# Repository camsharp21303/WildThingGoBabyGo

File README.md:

# WildThingGoBabyGo
All the files and designs for using a wild thing for Go Baby Go. Created from programming department on FTC team 10523 the dragons

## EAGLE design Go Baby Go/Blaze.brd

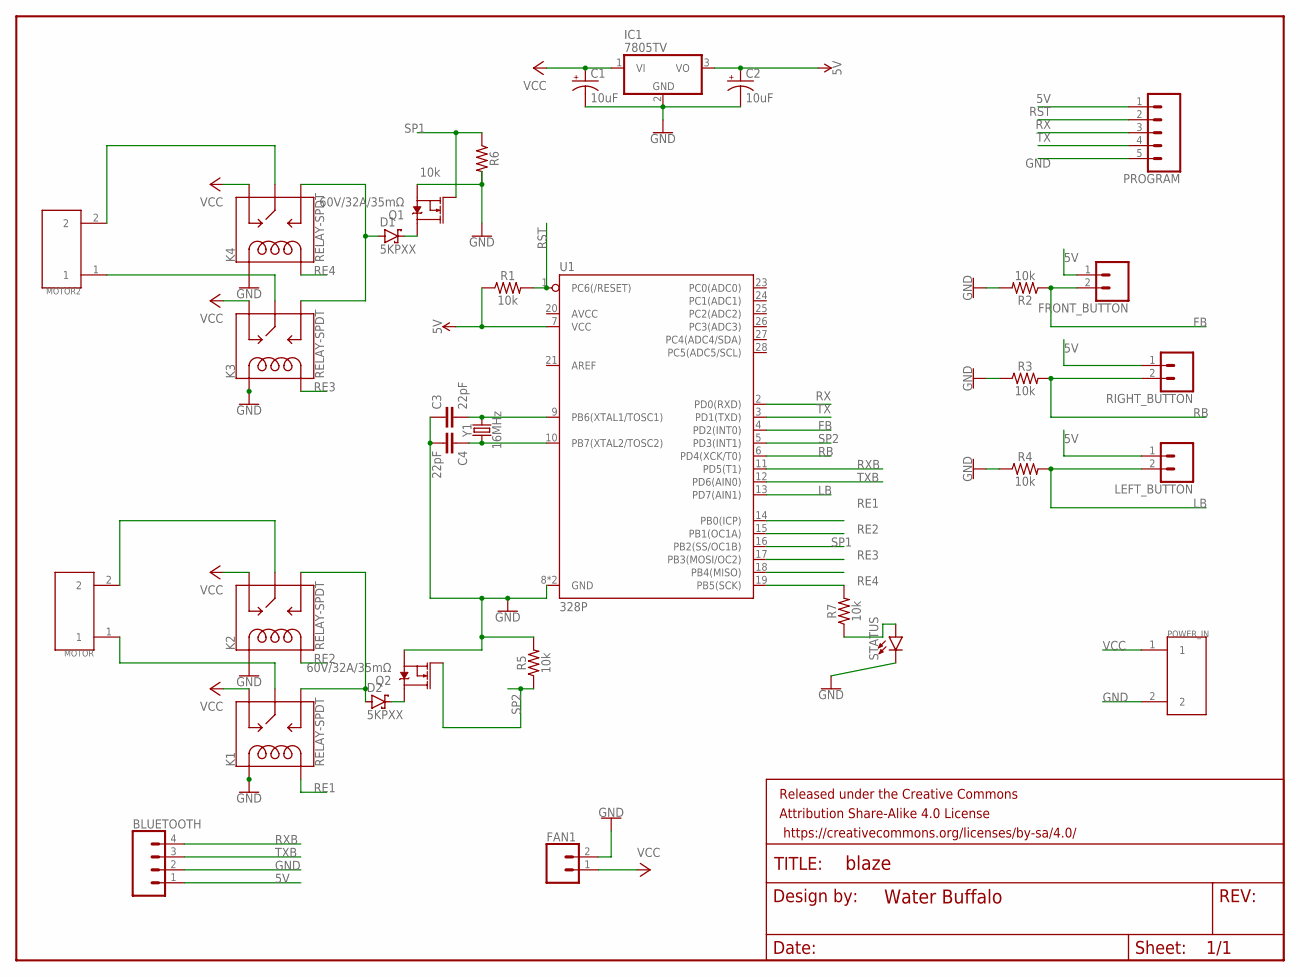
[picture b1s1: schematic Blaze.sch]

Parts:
BLUETOOTH: CONN_04PTH; 1X04
C1, C2: 10uF; CPOL-RADIAL-2.5MM-5MM
C3, C4: 22pF; CAP-PTH-2.54
D1, D2: 5KPXX; P6T15
FAN1: CONN_02; 1X02
FRAME1: FRAME-LETTERNO_PACKAGE; DUMMY
FRONT_BUTTON: CONN_02; 1X02
IC1: 7805TV; TO220V
K1, K2, K3, K4: RELAY-SPDT; RELAY_G5LE
LEFT_BUTTON: CONN_02; 1X02
MOTOR, MOTOR2: 10M_TERM; 10MM_TERM
POWER_IN: 10M_TERM; 10MM_TERM
PROGRAM: CONN_05; 1X05
Q1, Q2: 60V/32A/35mΩ; TO220V
R1, R2, R3, R4, R5, R6, R7: 10k; AXIAL-0.3
RIGHT_BUTTON: CONN_02; 1X02
STATUS: LED3MM; LED_3MM
U1: 328P; DIP28
Y1: 16MHz; HC49US

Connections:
5V: BLUETOOTH.1, C2.1 (+), FRONT_BUTTON.1, IC1.3 (VO), LEFT_BUTTON.1, PROGRAM.1, R1.P$1 (1), RIGHT_BUTTON.1, U1.7 (VCC)
FB: FRONT_BUTTON.2, R2.P$1 (1), U1.4 (PD2(INT0))
GND: BLUETOOTH.2, C1.2 (-), C2.2 (-), C3.1, C4.2, FAN1.2, IC1.2 (GND), K1.2 (COIL1), K2.2 (COIL1), K3.2 (COIL1), K4.2 (COIL1), POWER_IN.2, PROGRAM.5, Q1.3 (S), Q2.3 (S), R2.P$2 (2), R3.P$1 (1), R4.P$1 (1), R5.P$2 (2), R6.P$2 (2), STATUS.K (C), U1.8 (GND), U1.22 (GND)
LB: LEFT_BUTTON.2, R4.P$2 (2), U1.13 (PD7(AIN1))
MOTOR2_1: K3.1 (MAIN), MOTOR2.1
MOTOR2_2: K4.1 (MAIN), MOTOR2.2
unnamed: D2.A, K1.3 (NO), K2.3 (NO)
unnamed: D1.C, Q1.2 (D)
unnamed: K2.1 (MAIN), MOTOR.2
unnamed: K1.1 (MAIN), MOTOR.1
unnamed: R7.P$1 (1), STATUS.A
unnamed: D1.A, K3.3 (NO), K4.3 (NO)
unnamed: D2.C, Q2.2 (D)
unnamed: C3.2, U1.9 (PB6(XTAL1/TOSC1)), Y1.2
unnamed: C4.1, U1.10 (PB7(XTAL2/TOSC2)), Y1.1
RB: R3.P$2 (2), RIGHT_BUTTON.2, U1.6 (PD4(XCK/T0))
RE1: K1.5 (COIL2), U1.14 (PB0(ICP))
RE2: K2.5 (COIL2), U1.15 (PB1(OC1A))
RE3: K3.5 (COIL2), U1.17 (PB3(MOSI/OC2))
RE4: K4.5 (COIL2), U1.18 (PB4(MISO))
RST: PROGRAM.2, R1.P$2 (2), U1.1 (PC6(/RESET))
RX: PROGRAM.3, U1.2 (PD0(RXD))
RXB: BLUETOOTH.4, U1.11 (PD5(T1))
SP1: Q1.1 (G), R6.P$1 (1), U1.16 (PB2(SS/OC1B))
SP2: Q2.1 (G), R5.P$1 (1), U1.5 (PD3(INT1))
STAT_LED: R7.P$2 (2), U1.19 (PB5(SCK))
TX: PROGRAM.4, U1.3 (PD1(TXD))
TXB: BLUETOOTH.3, U1.12 (PD6(AIN0))
VCC: C1.1 (+), FAN1.1, IC1.1 (VI), K1.4 (NC), K2.4 (NC), K3.4 (NC), K4.4 (NC), POWER_IN.1

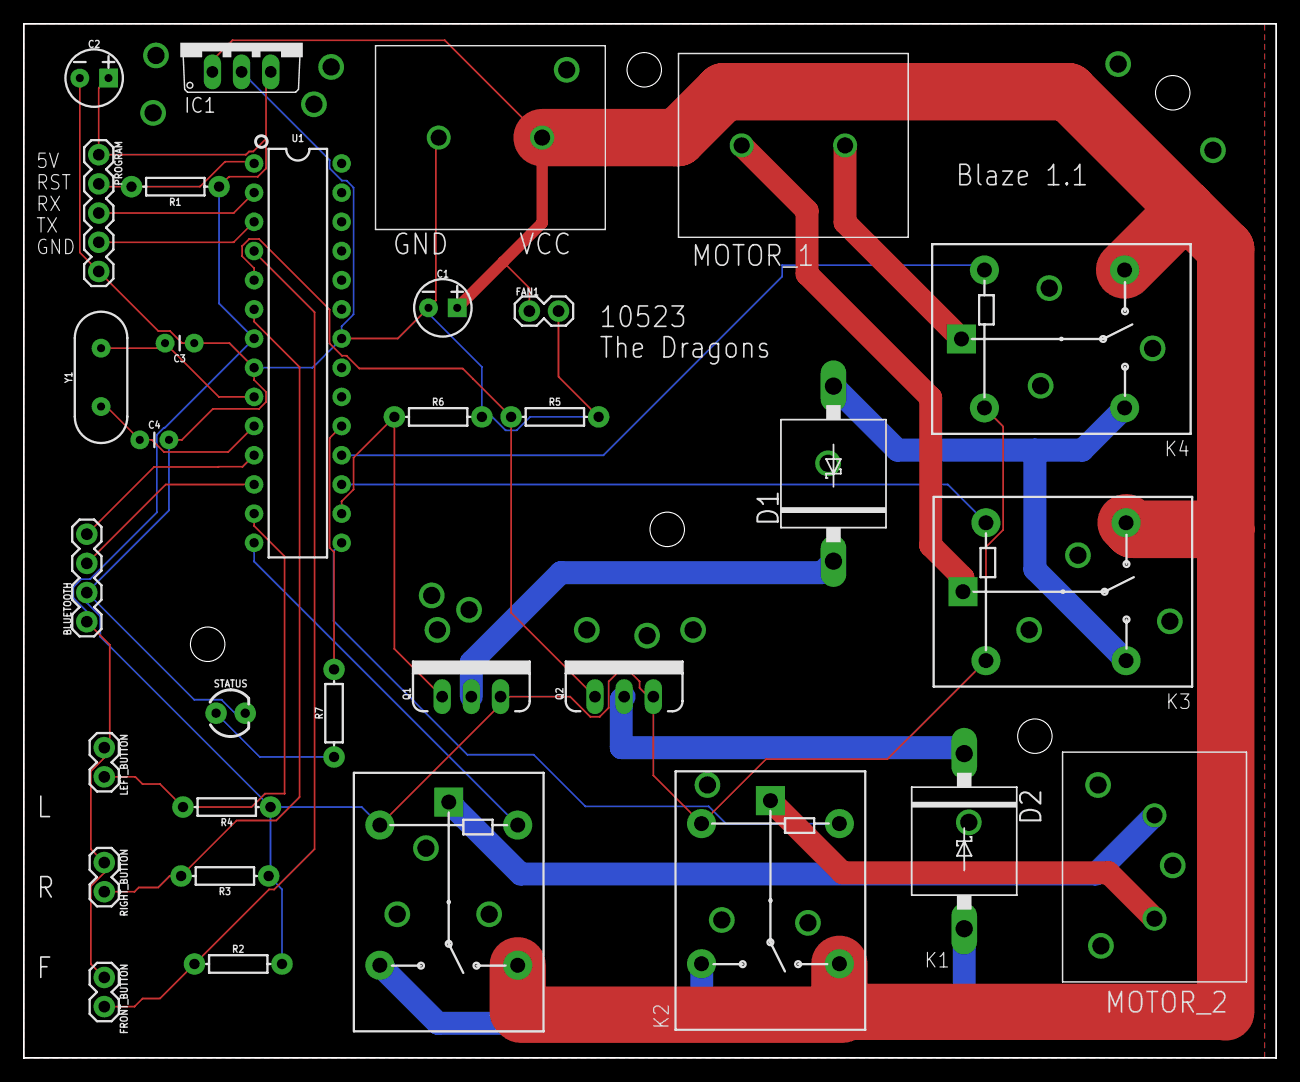
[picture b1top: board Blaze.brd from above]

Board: 2 copper layers, 109.0 x 90.0 mm, 33 parts (0 on the bottom side), 29 nets.

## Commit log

2020-10-28 added eagle files
2021-01-28 added submodules for code and app

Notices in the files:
parts and their libraries:
SparkFun-Connectors: Licensing: Creative Commons ShareAlike 4.0 International - https://creativecommons.org/licenses/by-sa/4.0
SparkFun-Aesthetics: Released under the Creative Commons Attribution Share-Alike 4.0 License
SparkFun-Aesthetics: https://creativecommons.org/licenses/by-sa/4.0
